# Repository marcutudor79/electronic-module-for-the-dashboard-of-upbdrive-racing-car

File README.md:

# ETTI-Bachelor's degree Applied Electronics

My Bachelor's degree that consists in research & design the following components:
- dashboard PCB with ESP32 SoC
- Test module PCB with Raspberry Pi Pico devboard
- Firmware for the ESP32 with ESP-IDF
- Firmware for the Raspberry Pi Pico with pico-sdk

# Thesis
The document can be referred [here.](Documentation/Thesis.pdf)

# Thesis summary
The thesis sumarry can be referred [here.](Documentation/Summary.pdf)

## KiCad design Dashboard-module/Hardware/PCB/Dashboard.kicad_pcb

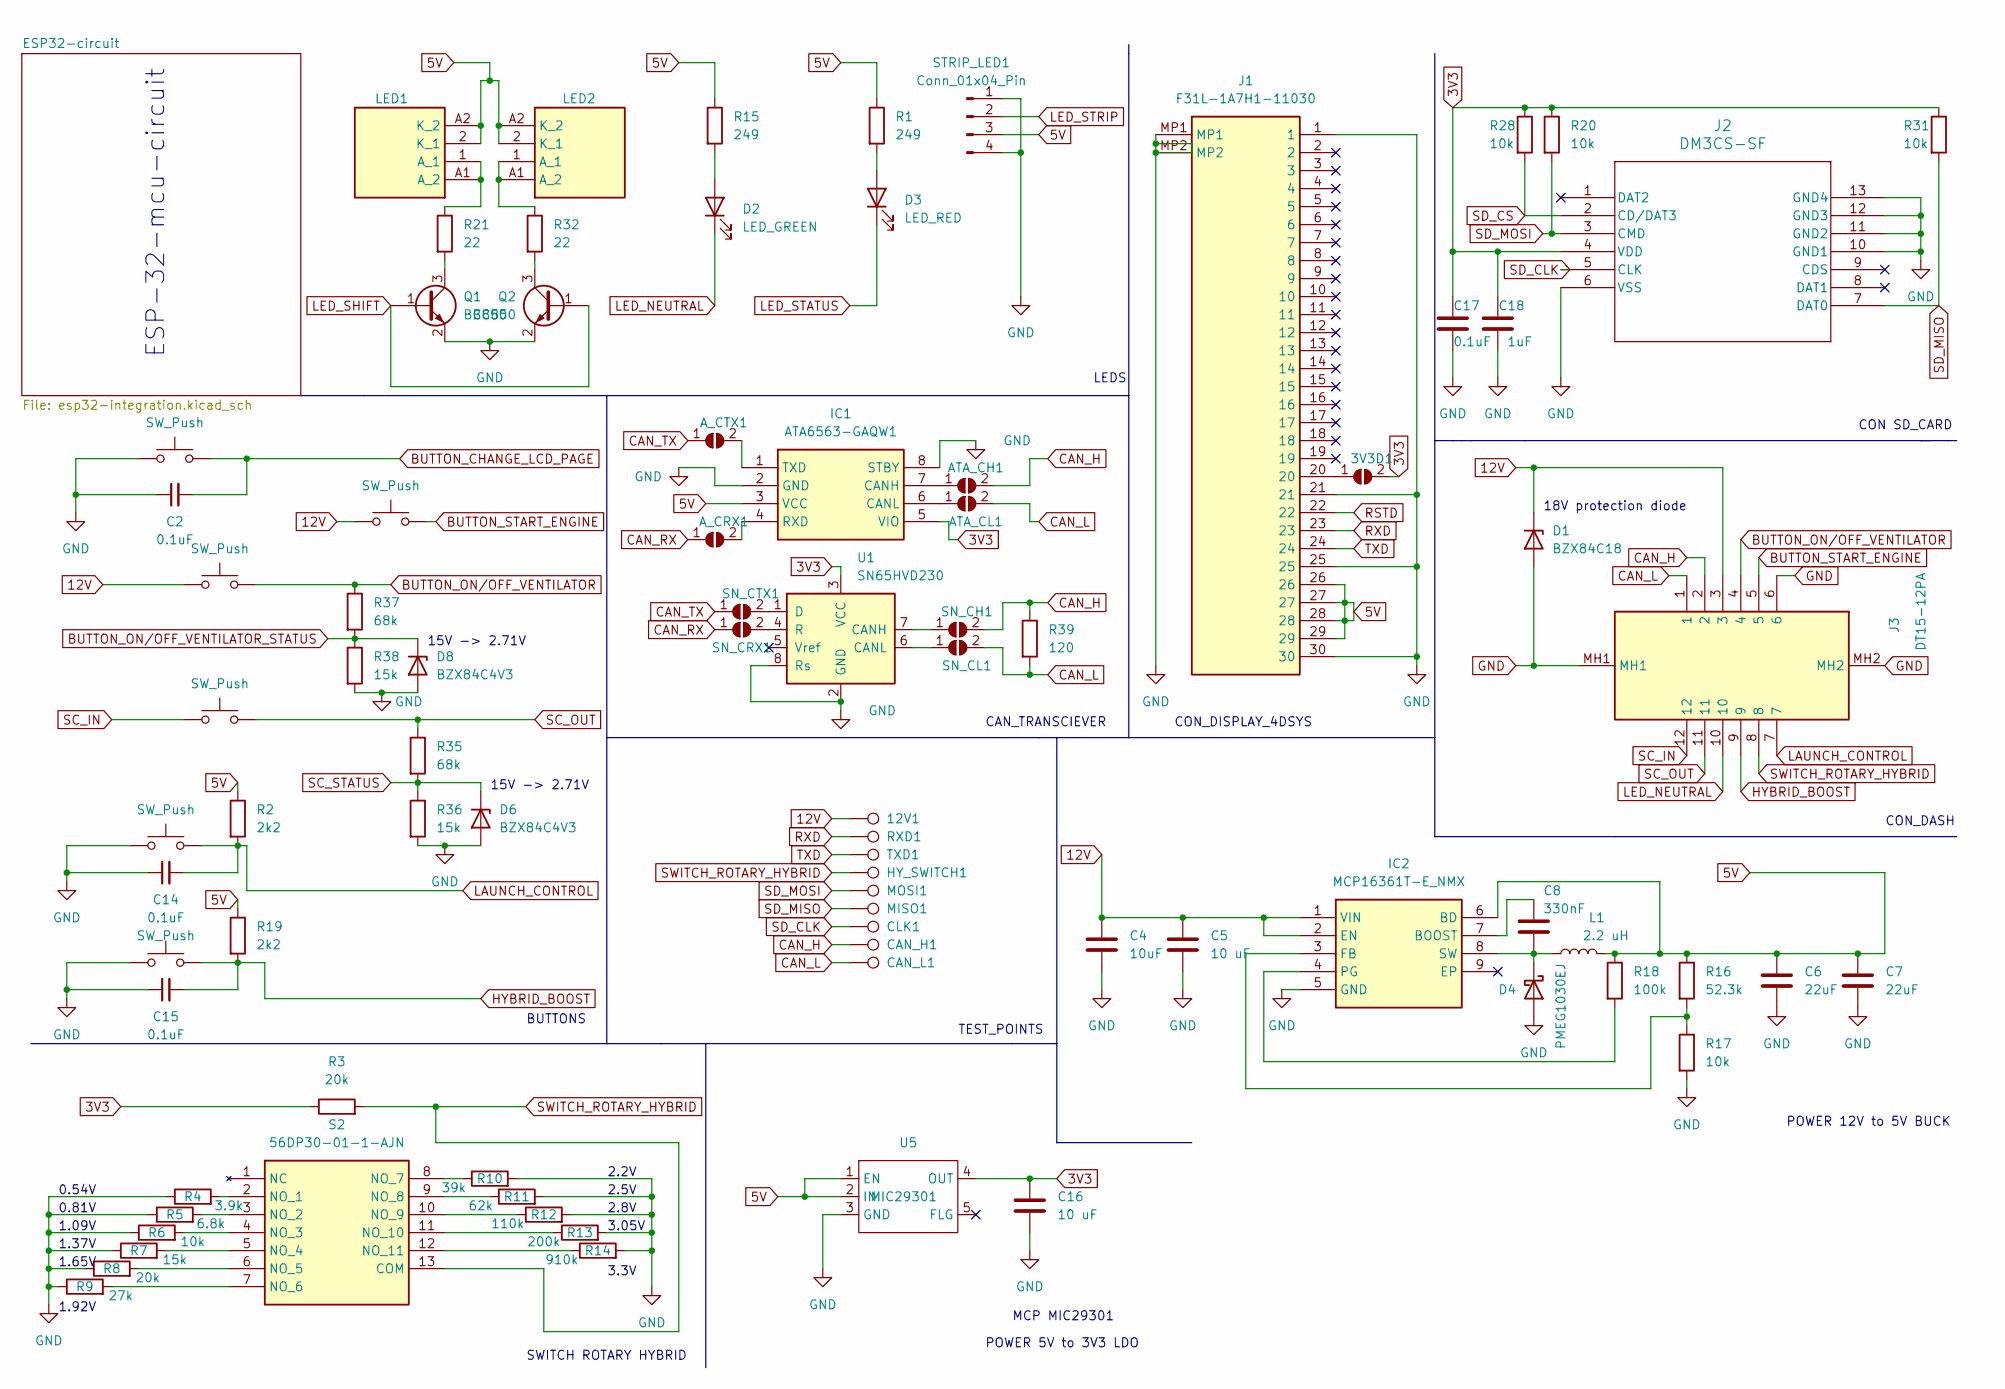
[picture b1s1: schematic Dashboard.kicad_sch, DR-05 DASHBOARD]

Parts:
3V3D1: SolderJumper_2_Open; SolderJumper-2_P1.3mm_Open_TrianglePad1.0x1.5mm
12V1: TestPoint; TestPoint_Pad_D2.0mm
ATA_CH1: SolderJumper_2_Open; SolderJumper-2_P1.3mm_Open_TrianglePad1.0x1.5mm
ATA_CL1: SolderJumper_2_Open; SolderJumper-2_P1.3mm_Open_TrianglePad1.0x1.5mm
A_CRX1: SolderJumper_2_Open; SolderJumper-2_P1.3mm_Open_TrianglePad1.0x1.5mm
A_CTX1: SolderJumper_2_Open; SolderJumper-2_P1.3mm_Open_TrianglePad1.0x1.5mm
BOOST1: SW_Push; PinHeader_1x02_P2.54mm_Vertical
C2, C14, C15, C17: 0.1uF; C_1210_3225Metric_Pad1.33x2.70mm_HandSolder
C4: 10uF; C_1210_3225Metric_Pad1.33x2.70mm_HandSolder
C5, C16: 10 uF; C_1210_3225Metric_Pad1.33x2.70mm_HandSolder
C6, C7: 22uF; C_1210_3225Metric_Pad1.33x2.70mm_HandSolder
C8: 330nF; C_1210_3225Metric_Pad1.33x2.70mm_HandSolder
C18: 1uF; C_1210_3225Metric_Pad1.33x2.70mm_HandSolder
CAN_H1: TestPoint; TestPoint_Pad_D2.0mm
CAN_L1: TestPoint; TestPoint_Pad_D2.0mm
CLK1: TestPoint; TestPoint_Pad_D2.0mm
D1: BZX84C18; SOT-23
D2: LED_GREEN; D_1210_3225Metric
D3: LED_RED; D_1210_3225Metric
D4: PMEG1030EJ; D_SOD-323_HandSoldering
D6, D8: BZX84C4V3; SOT-23
HY_SWITCH1: TestPoint; TestPoint_Pad_D2.0mm
IC1: ATA6563-GAQW1; SOIC127P600X175-8N; Mouser Part Number 579-ATA6563-GAQW1
IC2: MCP16361T-E_NMX; MCP16361TENMX; Mouser Part Number 579-MCP16361T-E/NMX
J1: F31L-1A7H1-11030; F31L1A7H111030; Mouser Part Number 649-F31L-1A7H1-11030
J2: DM3CS-SF; DM3CS_SF
J3: DT15-12PA; DT1512PA; Mouser Part Number 571-DT15-12PA
L1: 2.2 uH; L_Vishay_IHLP-5050
LAUNCH1: SW_Push; PinHeader_1x02_P2.54mm_Vertical
LED1, LED2: GR_PSLM31.23-FTGP-45-FG; GRPSLM3123FTGP45FG; Mouser Part Number 720-PSLM3123A4675
MISO1: TestPoint; TestPoint_Pad_D2.0mm
MOSI1: TestPoint; TestPoint_Pad_D2.0mm
PAGE1: SW_Push; PinHeader_1x02_P2.54mm_Vertical
Q1, Q2: BC850; SOT-23
R1, R15: 249; R_1210_3225Metric
R2, R19: 2k2; R_1210_3225Metric
R3, R8: 20k; R_1210_3225Metric_Pad1.30x2.65mm_HandSolder
R4: 3.9k; R_1210_3225Metric_Pad1.30x2.65mm_HandSolder
R5: 6.8k; R_1210_3225Metric_Pad1.30x2.65mm_HandSolder
R6, R17, R20, R28, R31: 10k; R_1210_3225Metric_Pad1.30x2.65mm_HandSolder
R7: 15k; R_1210_3225Metric_Pad1.30x2.65mm_HandSolder
R9: 27k; R_1210_3225Metric_Pad1.30x2.65mm_HandSolder
R10: 39k; R_1210_3225Metric_Pad1.30x2.65mm_HandSolder
R11: 62k; R_1210_3225Metric_Pad1.30x2.65mm_HandSolder
R12: 110k; R_1210_3225Metric_Pad1.30x2.65mm_HandSolder
R13: 200k; R_1210_3225Metric_Pad1.30x2.65mm_HandSolder
R14: 910k; R_1210_3225Metric_Pad1.30x2.65mm_HandSolder
R16: 52.3k; R_1210_3225Metric_Pad1.30x2.65mm_HandSolder
R18: 100k; R_1210_3225Metric_Pad1.30x2.65mm_HandSolder
R21, R32: 22; R_1210_3225Metric
R35, R37: 68k; R_1210_3225Metric
R36, R38: 15k; R_1210_3225Metric
R39: 120; R_1210_3225Metric_Pad1.30x2.65mm_HandSolder
RXD1: TestPoint; TestPoint_Pad_D2.0mm
S2: 56DP30-01-1-AJN; 56SP3001B12N; Mouser Part Number 706-56DP30-01-1-AJN
SC1: SW_Push; PinHeader_1x02_P2.54mm_Vertical
SN_CH1: SolderJumper_2_Open; SolderJumper-2_P1.3mm_Open_TrianglePad1.0x1.5mm
SN_CL1: SolderJumper_2_Open; SolderJumper-2_P1.3mm_Open_TrianglePad1.0x1.5mm
SN_CRX1: SolderJumper_2_Open; SolderJumper-2_P1.3mm_Open_TrianglePad1.0x1.5mm
SN_CTX1: SolderJumper_2_Open; SolderJumper-2_P1.3mm_Open_TrianglePad1.0x1.5mm
STRIP_LED1: Conn_01x04_Pin; PinSocket_1x04_P2.54mm_Vertical
S_ENG1: SW_Push; PinHeader_1x02_P2.54mm_Vertical
TXD1: TestPoint; TestPoint_Pad_D2.0mm
U1: SN65HVD230; SOIC-8_3.9x4.9mm_P1.27mm
U5: MIC29301; TO-220-5_Horizontal_TabDown
VENT1: SW_Push; PinHeader_1x02_P2.54mm_Vertical

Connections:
3V3: 3V3D1.2 (B), C16.1, C17.1, C18.1, IC1.5 (VIO), J2.4 (VDD), R3.1, R20.1, R28.1, R31.1, U1.3 (VCC), U5.4 (OUT); also elsewhere on the board
5V: C6.1, C7.1, IC1.3 (VCC), IC2.6 (BD), J1.26, J1.27, J1.28, J1.29, L1.2, LED1.2 (K_1), LED1.A2 (K_2), LED2.2 (K_1), LED2.A2 (K_2), R1.1, R2.1, R15.1, R16.1, R18.1, R19.1, STRIP_LED1.3, U5.1 (EN), U5.2 (IN); also elsewhere on the board
12V: 12V1.1, C4.1, C5.1, D1.3 (K), IC2.1 (VIN), IC2.2 (EN), J3.3, S_ENG1.2, VENT1.2
BUTTON_CHANGE_LCD_PAGE: C2.2, PAGE1.2; also elsewhere on the board
BUTTON_ON/OFF_VENTILATOR: J3.4, R37.1, VENT1.1
BUTTON_ON/OFF_VENTILATOR_STATUS: D8.3 (K), R37.2, R38.1; also elsewhere on the board
BUTTON_START_ENGINE: J3.5, S_ENG1.1
CAN_H: ATA_CH1.2 (B), CAN_H1.1, J3.2, R39.1, SN_CH1.2 (B)
CAN_L: ATA_CL1.2 (B), CAN_L1.1, J3.1, R39.2, SN_CL1.2 (B)
CAN_RX: A_CRX1.1 (A), SN_CRX1.1 (A); also elsewhere on the board
CAN_TX: A_CTX1.1 (A), SN_CTX1.1 (A); also elsewhere on the board
GND: BOOST1.2, C2.1, C4.2, C5.2, C6.2, C7.2, C14.1, C15.1, C16.2, C17.2, C18.2, D1.1 (A), D4.2 (A), D6.1 (A), D8.1 (A), IC1.2 (GND), IC1.8 (STBY), IC2.5 (GND), J1.1, J1.21, J1.25, J1.30, J1.MP1, J1.MP2, J2.6 (VSS), J2.10 (GND1), J2.11 (GND2), J2.12 (GND3), J2.13 (GND4), J3.6, J3.MH1, J3.MH2, LAUNCH1.2, PAGE1.1, Q1.2 (E), Q2.2 (E), R4.1, R5.1, R6.1, R7.1, R8.1, R9.1, R10.2, R11.2, R12.2, R13.2, R14.2, R17.2, R36.2, R38.2, STRIP_LED1.1, STRIP_LED1.4, U1.2 (GND), U1.8 (Rs), U5.3 (GND); also elsewhere on the board
HYBRID_BOOST: BOOST1.1, C15.2, J3.9, R19.2
LAUNCH_CONTROL: C14.2, J3.7, LAUNCH1.1, R2.2
LED_NEUTRAL: D2.1 (K), J3.10; also elsewhere on the board
LED_SHIFT: Q1.1 (B), Q2.1 (B); also elsewhere on the board
LED_STATUS: D3.1 (K); also elsewhere on the board
LED_STRIP: STRIP_LED1.2; also elsewhere on the board
unnamed: 3V3D1.1 (A), J1.20
unnamed: ATA_CH1.1 (A), IC1.7 (CANH)
unnamed: ATA_CL1.1 (A), IC1.6 (CANL)
unnamed: A_CRX1.2 (B), IC1.4 (RXD)
unnamed: A_CTX1.2 (B), IC1.1 (TXD)
unnamed: D2.2 (A), R15.2
unnamed: D3.2 (A), R1.2
unnamed: C8.2, D4.1 (K), IC2.8 (SW), L1.1
unnamed: C8.1, IC2.7 (BOOST)
unnamed: IC2.3 (FB), R16.2, R17.1
unnamed: IC2.4 (PG), R18.2
unnamed: LED1.1 (A_1), LED1.A1 (A_2), R21.1
unnamed: LED2.1 (A_1), LED2.A1 (A_2), R32.1
unnamed: Q1.3 (C), R21.2
unnamed: Q2.3 (C), R32.2
unnamed: R4.2, S2.2 (NO_1)
unnamed: R5.2, S2.3 (NO_2)
unnamed: R6.2, S2.4 (NO_3)
unnamed: R7.2, S2.5 (NO_4)
unnamed: R8.2, S2.6 (NO_5)
unnamed: R9.2, S2.7 (NO_6)
unnamed: R10.1, S2.8 (NO_7)
unnamed: R11.1, S2.9 (NO_8)
unnamed: R12.1, S2.10 (NO_9)
unnamed: R13.1, S2.11 (NO_10)
unnamed: R14.1, S2.12 (NO_11)
unnamed: SN_CH1.1 (A), U1.7 (CANH)
unnamed: SN_CL1.1 (A), U1.6 (CANL)
unnamed: SN_CRX1.2 (B), U1.4 (R)
unnamed: SN_CTX1.2 (B), U1.1 (D)
RSTD: J1.22; also elsewhere on the board
RXD: J1.23, RXD1.1; also elsewhere on the board
SC_IN: J3.12, SC1.2
SC_OUT: J3.11, R35.1, SC1.1
SC_STATUS: D6.3 (K), R35.2, R36.1; also elsewhere on the board
SD_CLK: CLK1.1, J2.5 (CLK); also elsewhere on the board
SD_CS: J2.2 (CD/DAT3), R28.2; also elsewhere on the board
SD_MISO: J2.7 (DAT0), MISO1.1, R31.2; also elsewhere on the board
SD_MOSI: J2.3 (CMD), MOSI1.1, R20.2; also elsewhere on the board
SWITCH_ROTARY_HYBRID: HY_SWITCH1.1, J3.8, R3.2, S2.13 (COM); also elsewhere on the board
TXD: J1.24, TXD1.1; also elsewhere on the board

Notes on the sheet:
2.2V
1.37V
BUTTONS
1.65V
TEST_POINTS
POWER 5V to 3V3 LDO
0.54V
CON SD_CARD
LEDS
3.3V
CON_DASH
CAN_TRANSCIEVER
15V -> 2.71V
0.81V
SWITCH ROTARY HYBRID
2.8V
CON_DISPLAY_4DSYS
1.92V
2.5V
1.09V
3.05V
ESP-32-mcu-circuit
POWER 12V to 5V BUCK
18V protection diode
MCP MIC29301

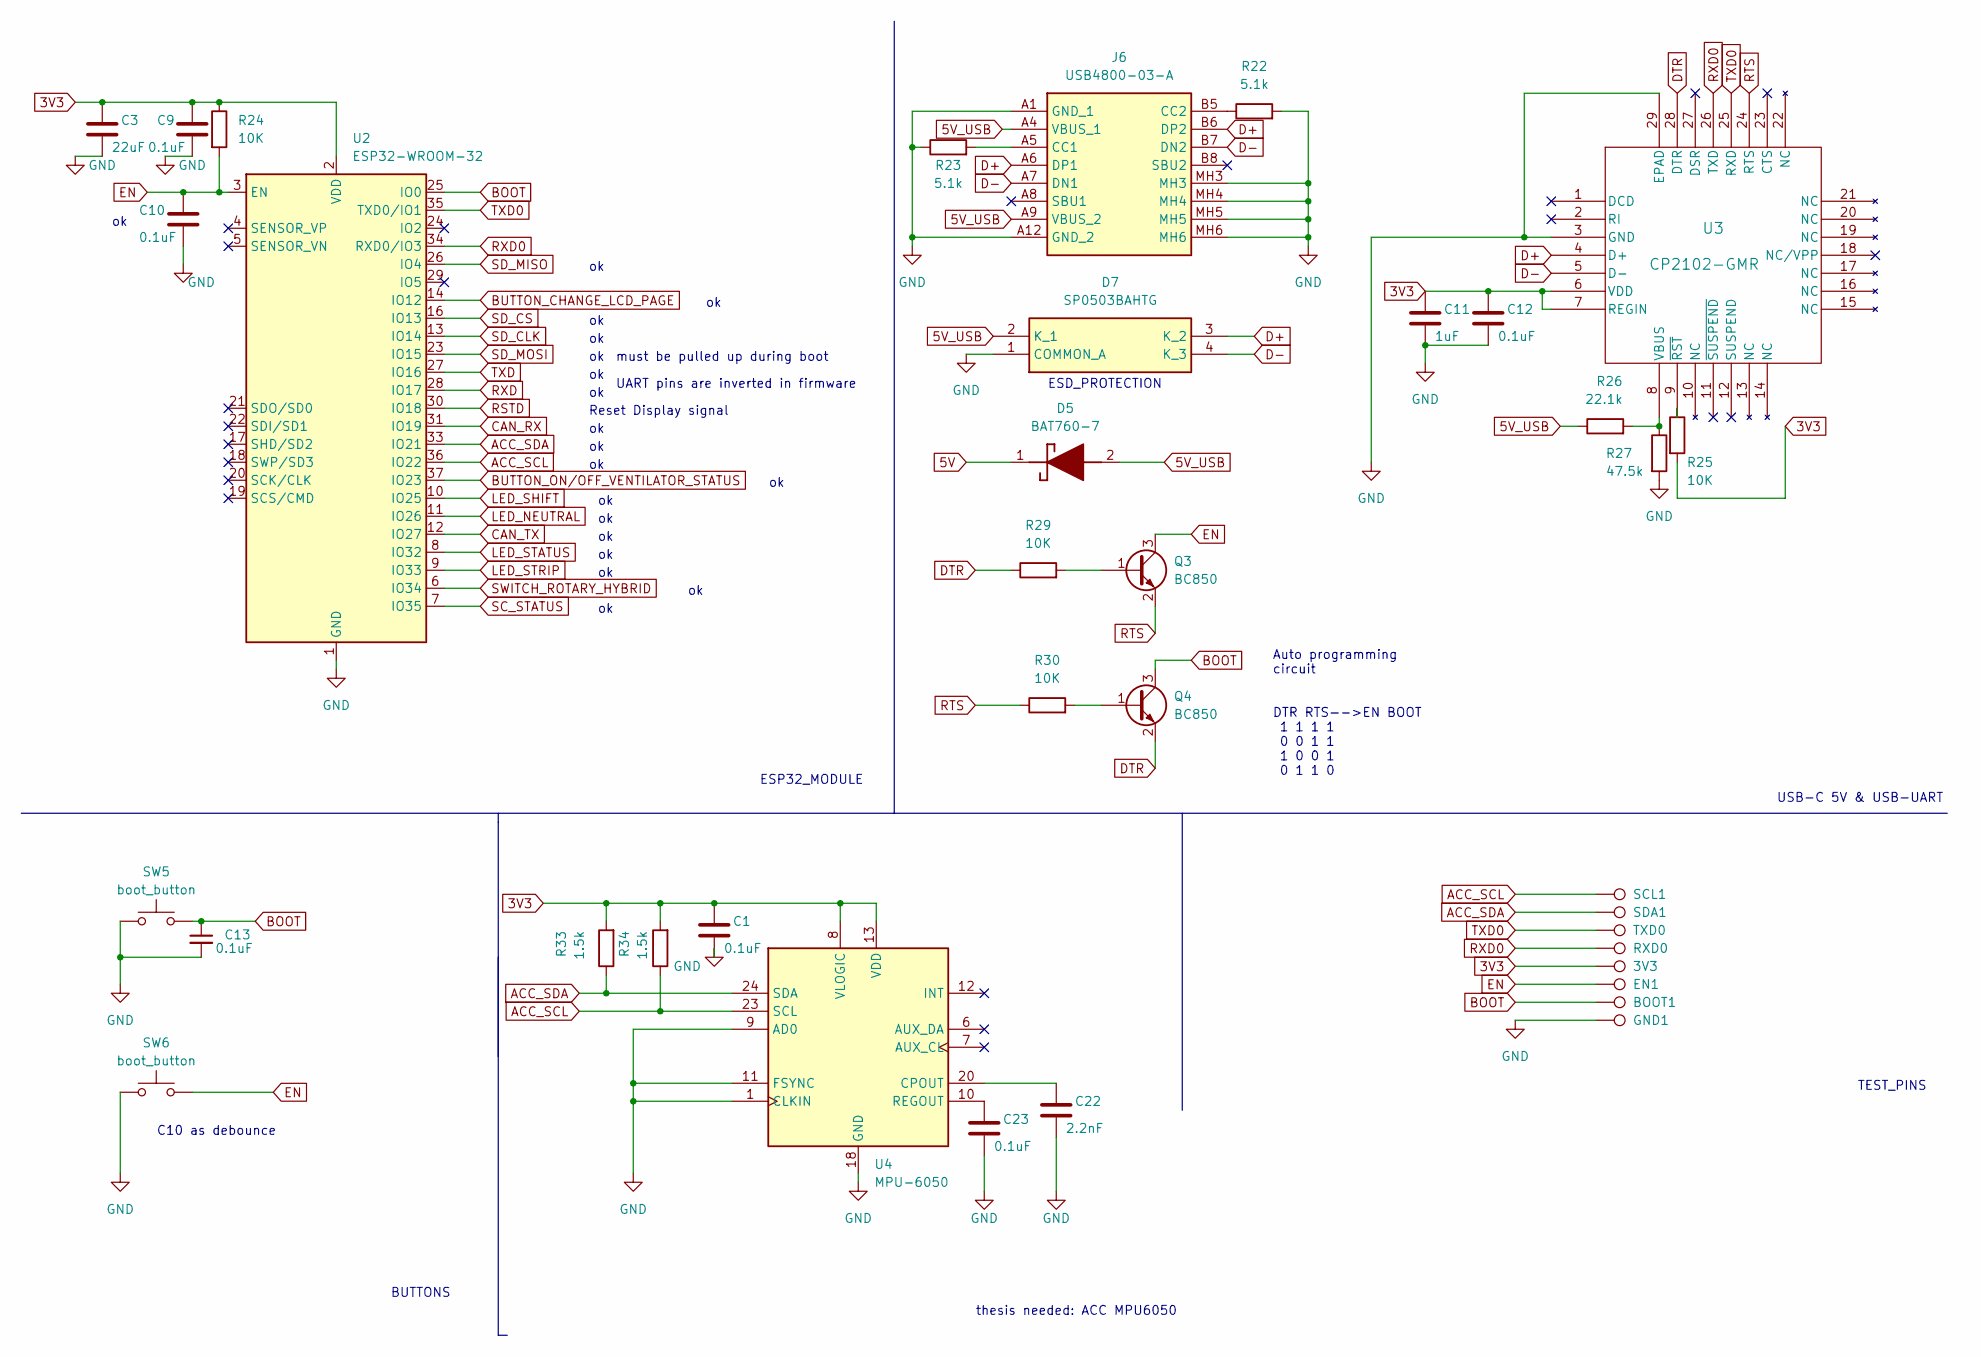
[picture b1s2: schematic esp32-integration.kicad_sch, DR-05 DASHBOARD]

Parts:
3V3: TestPoint; TestPoint_Pad_D2.0mm
BOOT1: TestPoint; TestPoint_Pad_D2.0mm
C1, C9, C10, C12, C23: 0.1uF; C_1210_3225Metric_Pad1.33x2.70mm_HandSolder
C3: 22uF; C_1210_3225Metric_Pad1.33x2.70mm_HandSolder
C11: 1uF; C_1210_3225Metric_Pad1.33x2.70mm_HandSolder
C13: 0.1uF; C_1210_3225Metric_Pad1.33x2.70mm_HandSolder; Manufacturer_Part_Number C1210C104K5RACAUTO
C22: 2.2nF; C_1210_3225Metric_Pad1.33x2.70mm_HandSolder
D5: BAT760-7; Mouser Part Number 621-BAT760-7
D7: SP0503BAHTG; Mouser Part Number 576-SP0503BAHTG
EN1: TestPoint; TestPoint_Pad_D2.0mm
GND1: TestPoint; TestPoint_Pad_D2.0mm
J6: USB4800-03-A; USB480003A; Mouser Part Number 640-USB4800-03-A
Q3, Q4: BC850; SOT-23
R22, R23: 5.1k; R_1210_3225Metric_Pad1.30x2.65mm_HandSolder
R24, R25, R29, R30: 10K; R_1210_3225Metric_Pad1.30x2.65mm_HandSolder
R26: 22.1k; R_1210_3225Metric_Pad1.30x2.65mm_HandSolder
R27: 47.5k; R_1210_3225Metric_Pad1.30x2.65mm_HandSolder
R33, R34: 1.5k; R_1210_3225Metric_Pad1.30x2.65mm_HandSolder
RXD0: TestPoint; TestPoint_Pad_D2.0mm
SCL1: TestPoint; TestPoint_Pad_D2.0mm
SDA1: TestPoint; TestPoint_Pad_D2.0mm
SW5, SW6: boot_button; SW_Tactile_SPST_NO_Straight_CK_PTS636Sx25SMTRLFS; Manufacturer_Part_Number PTS636 SK25 SMTR LFS
TXD0: TestPoint; TestPoint_Pad_D2.0mm
U2: ESP32-WROOM-32
U3: CP2102-GMR; QFN28_5X5_SIL
U4: MPU-6050; InvenSense_QFN-24_4x4mm_P0.5mm

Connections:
3V3: 3V3.1, C1.1, C3.1, C9.1, C11.1, C12.1, R24.1, R25.2, R33.2, R34.2, U2.2 (VDD), U3.6 (VDD), U3.7 (REGIN), U4.8 (VLOGIC), U4.13 (VDD); also elsewhere on the board
5V: D5.1 (K); also elsewhere on the board
5V_USB: D5.2 (A), D7.2 (K_1), J6.A4 (VBUS_1), J6.A9 (VBUS_2), R26.1
ACC_SCL: R34.1, SCL1.1, U2.36 (IO22), U4.23 (SCL)
ACC_SDA: R33.1, SDA1.1, U2.33 (IO21), U4.24 (SDA)
BOOT: BOOT1.1, C13.1, Q4.3 (C), SW5.2, U2.25 (IO0)
BUTTON_CHANGE_LCD_PAGE: U2.14 (IO12); also elsewhere on the board
BUTTON_ON/OFF_VENTILATOR_STATUS: U2.37 (IO23); also elsewhere on the board
CAN_RX: U2.31 (IO19); also elsewhere on the board
CAN_TX: U2.12 (IO27); also elsewhere on the board
D+: D7.3 (K_2), J6.A6 (DP1), J6.B6 (DP2), U3.4 (D+)
D-: D7.4 (K_3), J6.A7 (DN1), J6.B7 (DN2), U3.5 (D-)
DTR: Q4.2 (E), R29.1, U3.28 (DTR)
EN: C10.1, EN1.1, Q3.3 (C), R24.2, SW6.2, U2.3 (EN)
GND: C1.2, C3.2, C9.2, C10.2, C11.2, C12.2, C13.2, C22.2, C23.2, D7.1 (COMMON_A), GND1.1, J6.A1 (GND_1), J6.A12 (GND_2), J6.MH3, J6.MH4, J6.MH5, J6.MH6, R22.2, R23.1, R27.2, SW5.1, SW6.1, U2.1 (GND), U2.15 (GND), U2.38 (GND), U2.39 (GND), U3.3 (GND), U3.29 (EPAD), U4.1 (CLKIN), U4.9 (AD0), U4.11 (FSYNC), U4.18 (GND); also elsewhere on the board
LED_NEUTRAL: U2.11 (IO26); also elsewhere on the board
LED_SHIFT: U2.10 (IO25); also elsewhere on the board
LED_STATUS: U2.8 (IO32); also elsewhere on the board
LED_STRIP: U2.9 (IO33); also elsewhere on the board
unnamed: J6.A5 (CC1), R23.2
unnamed: J6.B5 (CC2), R22.1
unnamed: Q3.1 (B), R29.2
unnamed: Q4.1 (B), R30.2
unnamed: R26.2, R27.1, U3.8 (VBUS)
unnamed: R25.1, U3.9 (~RST)
unnamed: C22.1, U4.20 (CPOUT)
unnamed: C23.1, U4.10 (REGOUT)
RSTD: U2.30 (IO18); also elsewhere on the board
RTS: Q3.2 (E), R30.1, U3.24 (RTS)
RXD: U2.28 (IO17); also elsewhere on the board
RXD0: RXD0.1, U2.34 (RXD0/IO3), U3.26 (TXD)
SC_STATUS: U2.7 (IO35); also elsewhere on the board
SD_CLK: U2.13 (IO14); also elsewhere on the board
SD_CS: U2.16 (IO13); also elsewhere on the board
SD_MISO: U2.26 (IO4); also elsewhere on the board
SD_MOSI: U2.23 (IO15); also elsewhere on the board
SWITCH_ROTARY_HYBRID: U2.6 (IO34); also elsewhere on the board
TXD: U2.27 (IO16); also elsewhere on the board
TXD0: TXD0.1, U2.35 (TXD0/IO1), U3.25 (RXD)

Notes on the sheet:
Auto programming circuit DTR RTS-->EN BOOT 1 1 1 1 0 0 1 1 1 0 0 1 0 1 1 0
C10 as debounce
ESP32_MODULE
ESD_PROTECTION
BUTTONS
must be pulled up during boot
USB-C 5V & USB-UART
thesis needed: ACC MPU6050
Reset Display signal
TEST_PINS
UART pins are inverted in firmware

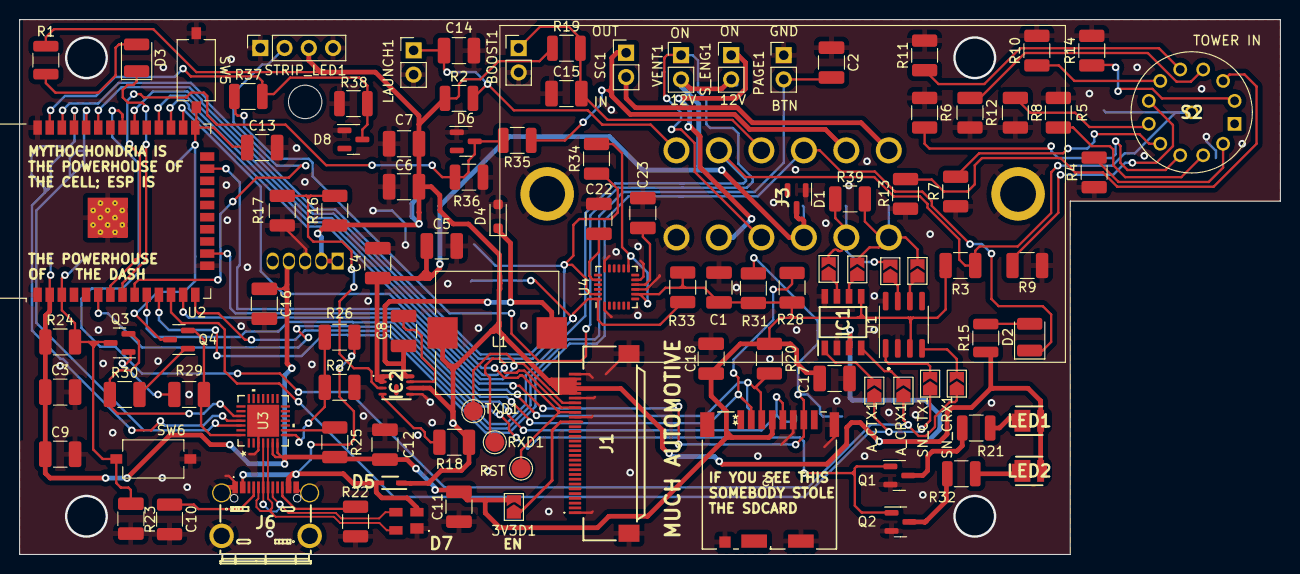
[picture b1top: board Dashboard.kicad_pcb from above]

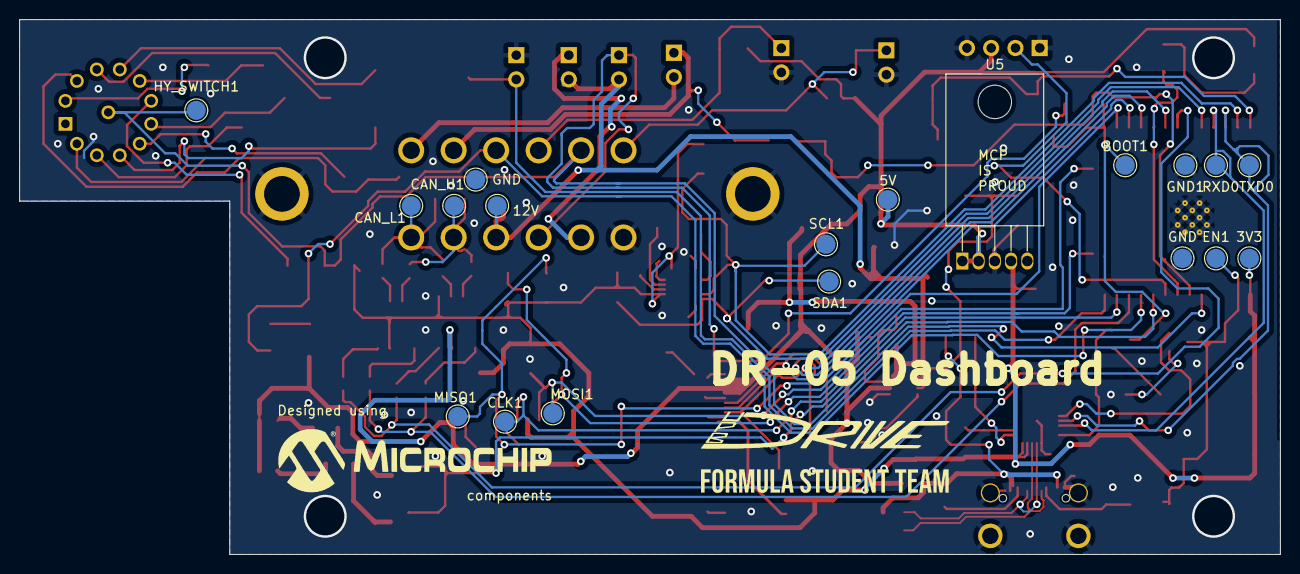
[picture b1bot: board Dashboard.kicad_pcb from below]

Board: 2 copper layers, 132.0 x 56.0 mm, 125 parts (19 on the bottom side), 78 nets.

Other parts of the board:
5V: TestPoint; TestPoint_Pad_D2.0mm
GND: TestPoint; TestPoint_Pad_D2.0mm
GND#2: TestPoint; TestPoint_Pad_D2.0mm
RST: TestPoint; TestPoint_Pad_D2.0mm

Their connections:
5V: 5V.1; also elsewhere on the board
GND: GND.1, GND#2.1; also elsewhere on the board
RSTD: RST.1; also elsewhere on the board

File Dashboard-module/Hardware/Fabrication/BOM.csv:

"Reference","Value","Mouser Price/Stock","Qty"
"3V3","TestPoint","","1"
"3V3D1","SolderJumper_2_Open","","1"
"12V1","TestPoint","","1"
"ATA_CH1","SolderJumper_2_Open","","1"
"ATA_CL1","SolderJumper_2_Open","","1"
"A_CRX1","SolderJumper_2_Open","","1"
"A_CTX1","SolderJumper_2_Open","","1"
"BOOST1","SW_Push","","1"
"BOOT1","TestPoint","","1"
"C1, C2, C9, C10, C12-C15, C17, C23","0.1uF","https://ro.mouser.com/ProductDetail/KEMET/C1210C104K5RACAUTO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","10"
"C3, C6, C7","22uF","https://www.mouser.co.uk/ProductDetail/Samsung-Electro-Mecha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","3"
"C4","10uF","https://www.mouser.co.uk/ProductDetail/Samsung-Electro-Mecha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","1"
"C5, C16","10 uF","https://www.mouser.co.uk/ProductDetail/Samsung-Electro-Mecha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","2"
"C8","330nF","https://ro.mouser.com/ProductDetail/KEMET/C1210C334J3RACTU?q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","1"
"C11, C18","1uF","https://ro.mouser.com/ProductDetail/KEMET/C1210C105K5RACAUTO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","2"
"C22","2.2nF","https://ro.mouser.com/ProductDetail/KEMET/C1210C222KGRACAUTO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","1"
"CAN_H1","TestPoint","","1"
"CAN_L1","TestPoint","","1"
"CLK1","TestPoint","","1"
"D1","BZX84C18","https://eu.mouser.com/ProductDetail/Diotec-Semiconductor/BZX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","1"
"D2","LED_GREEN","https://www.mouser.co.uk/ProductDetail/Broadcom-Avago/ASMT-B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","1"
"D3","LED_RED","https://www.mouser.co.uk/ProductDetail/Broadcom-Avago/ASMT-B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","1"
"D4","PMEG1030EJ","https:/ro.mouser.com/ProductDetail/Nexperia/PMEG1030EJ115?qs=LOCUfHb8d9vmk7P%2FuYbs5A%3D%3D","1"
"D5","BAT760-7","https://www.mouser.co.uk/ProductDetail/Diodes-Incorporated/B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","1"
"D6, D8","BZX84C4V3","https://eu.mouser.com/ProductDetail/Diotec-Semiconductor/BZX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","2"
"D7","SP0503BAHTG","https://www.mouser.co.uk/ProductDetail/Littelfuse/SP0503BAHT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","1"
"EN1","TestPoint","","1"
"GND1","TestPoint","","1"
"HY_SWITCH1","TestPoint","","1"
"IC1","ATA6563-GAQW1","https://www.mouser.co.uk/ProductDetail/Microchip-Technology/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","1"
"IC2","MCP16361T-E_NMX","https://www.mouser.co.uk/ProductDetail/Microchip-Technology/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","1"
"J1","F31L-1A7H1-11030","https://www.mouser.co.uk/ProductDetail/Amphenol-Aorora/F31L-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","1"
"J2","DM3CS-SF","https://eu.mouser.com/ProductDetail/Hirose-Connector/DM3CS-S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","1"
"J3","DT15-12PA","https://www.mouser.co.uk/ProductDetail/TE-Connectivity-DEUTS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","1"
"J6","USB4800-03-A","https://www.mouser.co.uk/ProductDetail/GCT/USB4800-03-A?qs=v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","1"
"L1","2.2 uH","https://www.mouser.co.uk/ProductDetail/Vishay-Dale/IHLP5050C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","1"
"LAUNCH1","SW_Push","","1"
"LED1, LED2","GR_PSLM31.23-FTGP-45-FG","https://www.mouser.co.uk/ProductDetail/OSRAM-Opto-Semiconduc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","2"
"MISO1","TestPoint","","1"
"MOSI1","TestPoint","","1"
"PAGE1","SW_Push","","1"
"Q1-Q4","BC850","https://www.mouser.co.uk/ProductDetail/Infineon-Technologies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","4"
"R1, R15","249","https://www.mouser.co.uk/ProductDetail/YAGEO/AC1210FR-07249R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","2"
"R2, R19","2k2","https://www.mouser.co.uk/ProductDetail/YAGEO/RC1210JR-072K2L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","2"
"R3, R8","20k","https://www.mouser.co.uk/c/passive-components/resistors/film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","2"
"R4","3.9k","https://www.mouser.co.uk/ProductDetail/YAGEO/AC1210FR-073K9L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","1"
"R5","6.8k","https://www.mouser.co.uk/ProductDetail/YAGEO/AC1210JR-076K8L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","1"
"R6, R17, R20, R28, R31","10k","-- mixed values --","5"
"R7, R36, R38","15k","-- mixed values --","3"
"R9","27k","https://www.mouser.co.uk/ProductDetail/YAGEO/RC1210JR-0727KL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","1"
"R10","39k","https://www.mouser.co.uk/ProductDetail/YAGEO/AC1210FR-0739KL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","1"
"R11","62k","https://www.mouser.co.uk/ProductDetail/YAGEO/RC1210FR-0762KL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","1"
"R12","110k","https://www.mouser.co.uk/ProductDetail/YAGEO/RC1210FR-07110K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","1"
"R13","200k","https://www.mouser.co.uk/ProductDetail/YAGEO/RC1210JR-07200K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","1"
"R14","910k","https://www.mouser.co.uk/c/passive-components/resistors/film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","1"
"R16","52.3k","https://ro.mouser.com/ProductDetail/Panasonic/ERJ-14NF5232U?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","1"
"R18","100k","https://ro.mouser.com/c/?q=RC1210FR-07100KL","1"
"R21, R32","22","https://www.mouser.co.uk/ProductDetail/YAGEO/AC1210JR-0722RL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","2"
"R22, R23","5.1k","https://www.mouser.co.uk/ProductDetail/YAGEO/RC1210FR-075K1L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","2"
"R24, R25, R29, R30","10K","https://ro.mouser.com/ProductDetail/SEI-Stackpole/RMCF1210FT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","4"
"R26","22.1k","https://ro.mouser.com/ProductDetail/Vishay-Dale/CRCW121022K1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","1"
"R27","47.5k","https://ro.mouser.com/ProductDetail/Vishay-Dale/CRCW121047K5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","1"
"R33, R34","1.5k","https://www.mouser.co.uk/ProductDetail/YAGEO/RC1210JR-071K5L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","2"
"R35, R37","68k","-- mixed values --","2"
"R39","120","https://www.mouser.co.uk/ProductDetail/YAGEO/RC1210JR-13120R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","1"
"RXD0, RXD1","TestPoint","","2"
"S2","56DP30-01-1-AJN","https://www.mouser.co.uk/ProductDetail/Grayhill/56DP30-01-1-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","1"
"SC1","SW_Push","","1"
"SCL1","TestPoint","","1"
"SDA1","TestPoint","","1"
"SN_CH1","SolderJumper_2_Open","","1"
"SN_CL1","SolderJumper_2_Open","","1"
"SN_CRX1","SolderJumper_2_Open","","1"
"SN_CTX1","SolderJumper_2_Open","","1"
"STRIP_LED1","Conn_01x04_Pin","https://www.mouser.co.uk/ProductDetail/Harwin/M20-9992046?qs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","1"
"SW5, SW6","boot_button","https://ro.mouser.com/ProductDetail/CK/PTS636-SK25-SMTR-LFS?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","2"
"S_ENG1","SW_Push","","1"
"TXD0, TXD1","TestPoint","","2"
"U1","SN65HVD230","https://eu.mouser.com/ProductDetail/Texas-Instruments/SN65HV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","1"
"U2","ESP32-WROOM-32","https://ro.mouser.com/ProductDetail/Espressif-Systems/ESP32-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","1"
"U3","CP2102-GMR","https://ro.mouser.com/ProductDetail/Silicon-Labs/CP2102-GMR?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","1"
"U4","MPU-6050","https://www.mouser.co.uk/ProductDetail/TDK-InvenSense/MPU-60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","1"
"U5","MIC29301","","1"
"VENT1","SW_Push","","1"

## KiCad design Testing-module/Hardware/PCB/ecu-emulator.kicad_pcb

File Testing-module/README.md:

# ECU Emulator

## Description
In order to debug the CAN bus as well as the dashboard module, this ECU Emulator
injects CAN packets into the CAN bus. It is a replacement for the ECU itself, because
we cannot use it just for electronics debugging, it has to be mounted in the FS car.

## How does it work
This ECU Emulator uses a potentiometer to emulate the accelerator pedal of the FS car
as well as a button to emulate the gear shift. The potentiometer is read via the built-in
ADC module of the Raspberry Pi Pico board, and the button is read using GPIO functions.

### How is the data generated
- rpm is generated using a constant 800 + the potentiometer value + a random number
between 0 - 49 in order to emulate the actual rpm of the FS car. The expected range is
between 800 - 13000.
- current gear is initially 0 (netural) and incremented when the button is pressed, until 4,
then it is set back to 0.
- all the other data is assigned the saw tooth signal between 0 - 250.

The CAN packets are formatted with respect to the CAN Packet allocation excel and then sent via the CAN bus.

## Project structure
```
- Docs     /* folder the documentation files */
- Firmware /
            - components/ - adc                 /* part of the code that enables the onboard
                                                    adc and configures a gpio to read a button */
                          - can                 /* part of the code that enables can communication
                                                    via the can bus transciever
                                                    also formats the packets according to the CAN
                                                    packet allocation */
                          - common              /* contains a header file in which the pins used
                                                    in the project are defined */
                          - heartbeat           /* part of the code that enables the built-in LED
                                                    to blink, for debug purposes */
                          - signal-generation   /* part of the code that generates the rpm data,
                                                   CurrentGear data and a sawtooth signal that
                                                   will replace the other data in the CAN packets */
            - main                /* contains the main source and header file with
                                    which describes the main loop of the program */
            - modules             /* contains can2040 git submodule that enables
                                     the PICO to communicate via CAN using bit banging
                                     on GPIOs */

- README.md /* project README file */
```

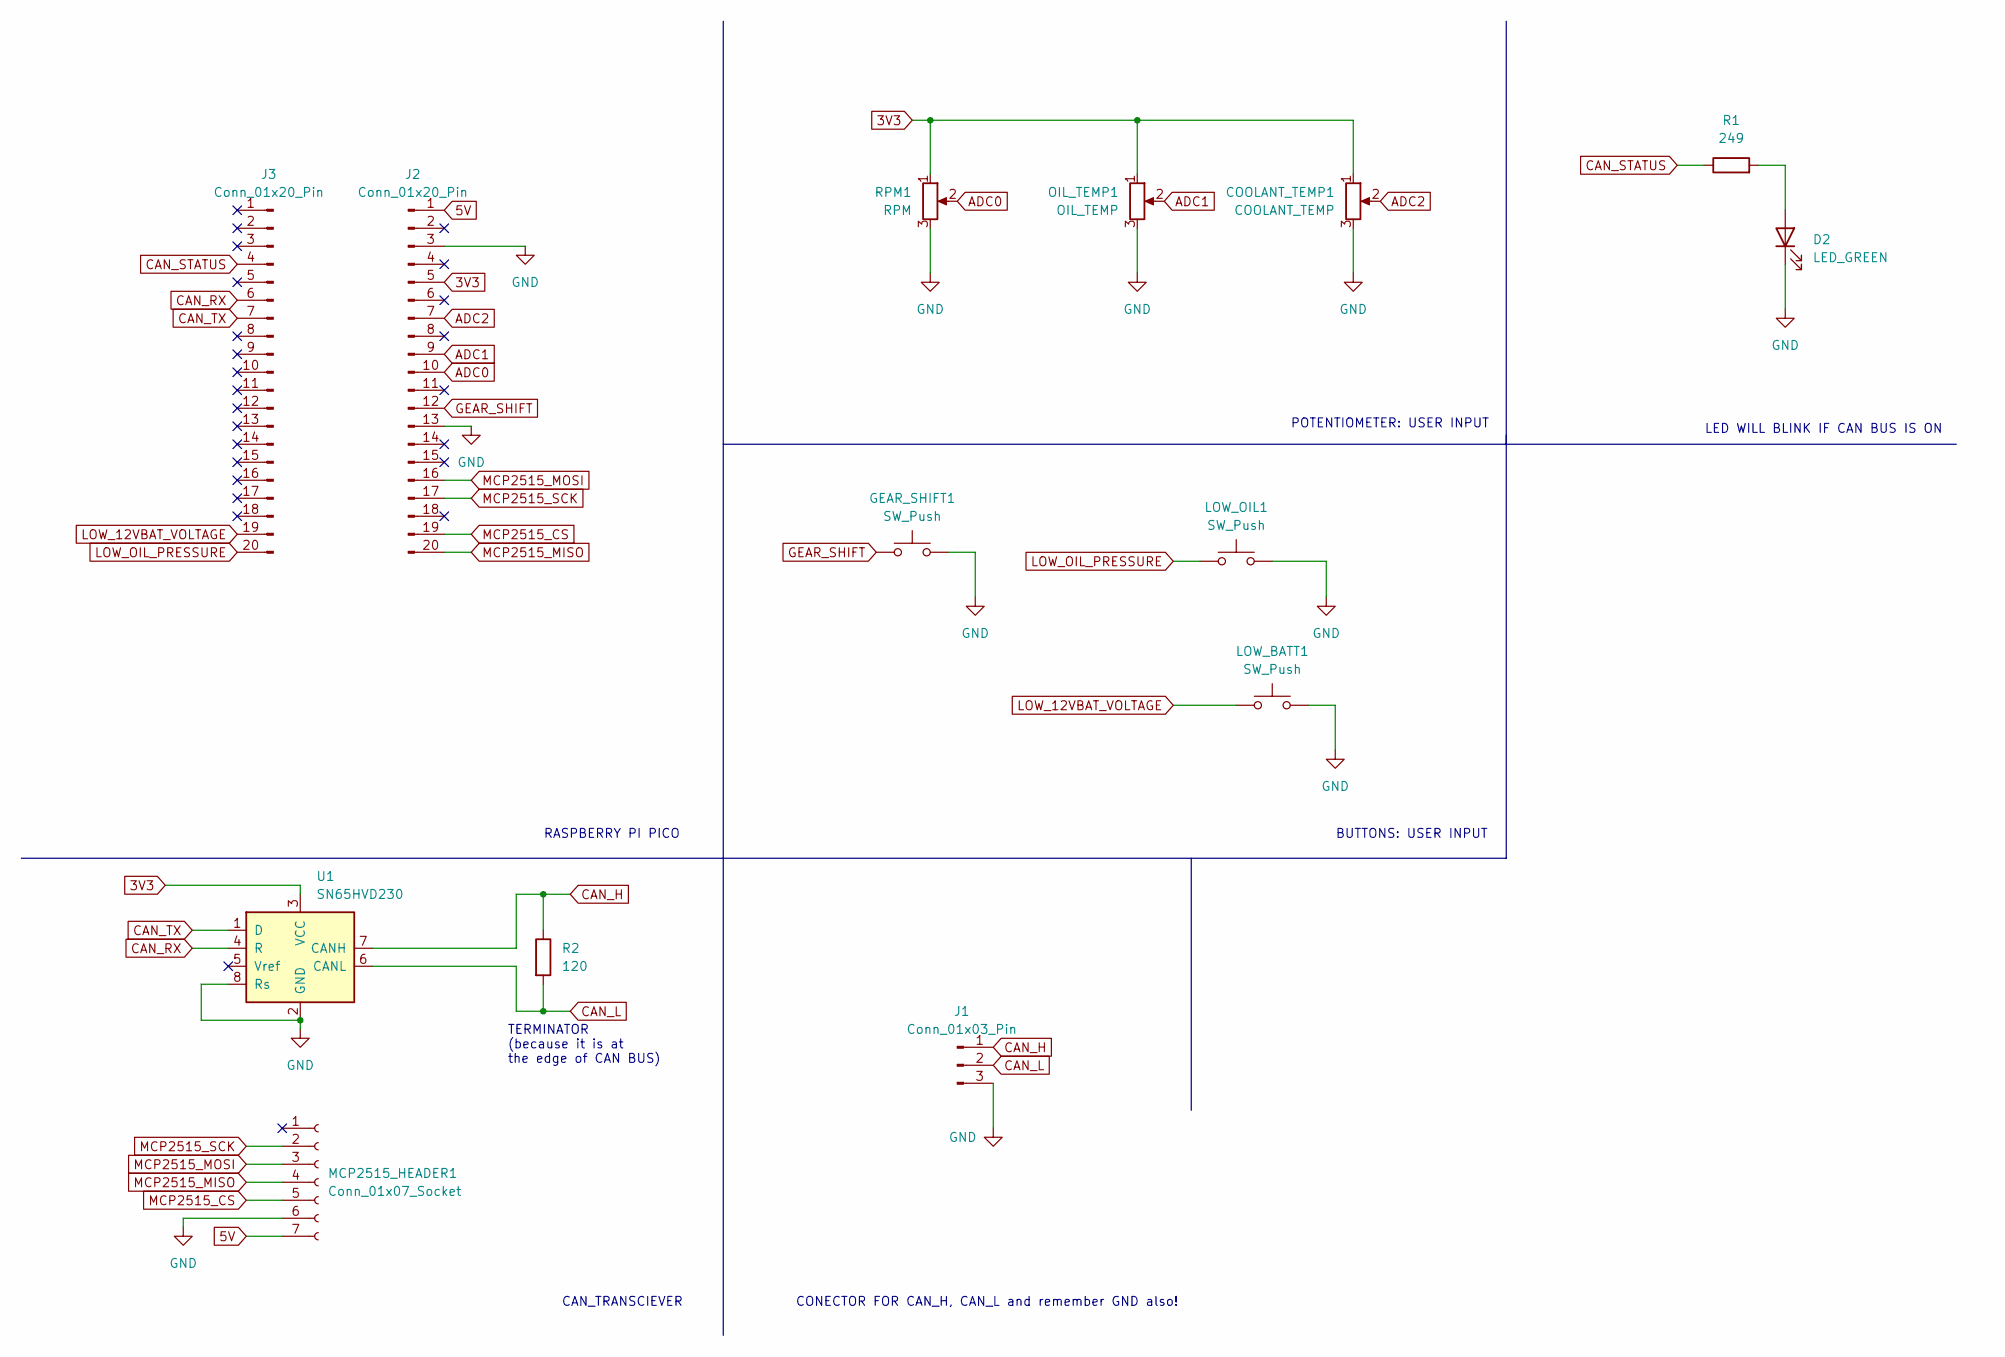
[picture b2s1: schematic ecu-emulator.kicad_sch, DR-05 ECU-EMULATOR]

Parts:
COOLANT_TEMP1: COOLANT_TEMP; Potentiometer_Alps_RK163_Single_Horizontal
D2: LED_GREEN; D_1210_3225Metric
GEAR_SHIFT1: SW_Push; SW_PUSH_6mm
J1: Conn_01x03_Pin; PinHeader_1x03_P2.54mm_Vertical
J2, J3: Conn_01x20_Pin; PinHeader_1x20_P2.54mm_Vertical
LOW_BATT1: SW_Push; SW_PUSH_6mm
LOW_OIL1: SW_Push; SW_PUSH_6mm
MCP2515_HEADER1: Conn_01x07_Socket; PinHeader_1x07_P2.54mm_Vertical
OIL_TEMP1: OIL_TEMP; Potentiometer_Alps_RK163_Single_Horizontal
R1: 249; R_1210_3225Metric_Pad1.30x2.65mm_HandSolder
R2: 120; R_1210_3225Metric_Pad1.30x2.65mm_HandSolder
RPM1: RPM; Potentiometer_Alps_RK163_Single_Horizontal
U1: SN65HVD230; SOIC-8_3.9x4.9mm_P1.27mm

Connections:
3V3: COOLANT_TEMP1.1, J2.5, OIL_TEMP1.1, RPM1.1, U1.3 (VCC)
5V: J2.1, MCP2515_HEADER1.7
ADC0: J2.10, RPM1.2
ADC1: J2.9, OIL_TEMP1.2
ADC2: COOLANT_TEMP1.2, J2.7
CAN_H: J1.1, R2.1, U1.7 (CANH)
CAN_L: J1.2, R2.2, U1.6 (CANL)
CAN_RX: J3.6, U1.4 (R)
CAN_STATUS: J3.4, R1.1
CAN_TX: J3.7, U1.1 (D)
GEAR_SHIFT: GEAR_SHIFT1.1, J2.12
GND: COOLANT_TEMP1.3, GEAR_SHIFT1.2, J1.3, J2.3, J2.13, LOW_BATT1.2, LOW_OIL1.2, MCP2515_HEADER1.6, OIL_TEMP1.3, RPM1.3, U1.2 (GND), U1.8 (Rs); also elsewhere on the board
LOW_12VBAT_VOLTAGE: J3.19, LOW_BATT1.1
LOW_OIL_PRESSURE: J3.20, LOW_OIL1.1
MCP2515_CS: J2.19, MCP2515_HEADER1.5
MCP2515_MISO: J2.20, MCP2515_HEADER1.4
MCP2515_MOSI: J2.16, MCP2515_HEADER1.3
MCP2515_SCK: J2.17, MCP2515_HEADER1.2
unnamed 18: R1.2; also elsewhere on the board

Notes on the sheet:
TERMINATOR (because it is at the edge of CAN BUS)
LED WILL BLINK IF CAN BUS IS ON
CAN_TRANSCIEVER
CONECTOR FOR CAN_H, CAN_L and remember GND also!
POTENTIOMETER: USER INPUT
RASPBERRY PI PICO
BUTTONS: USER INPUT

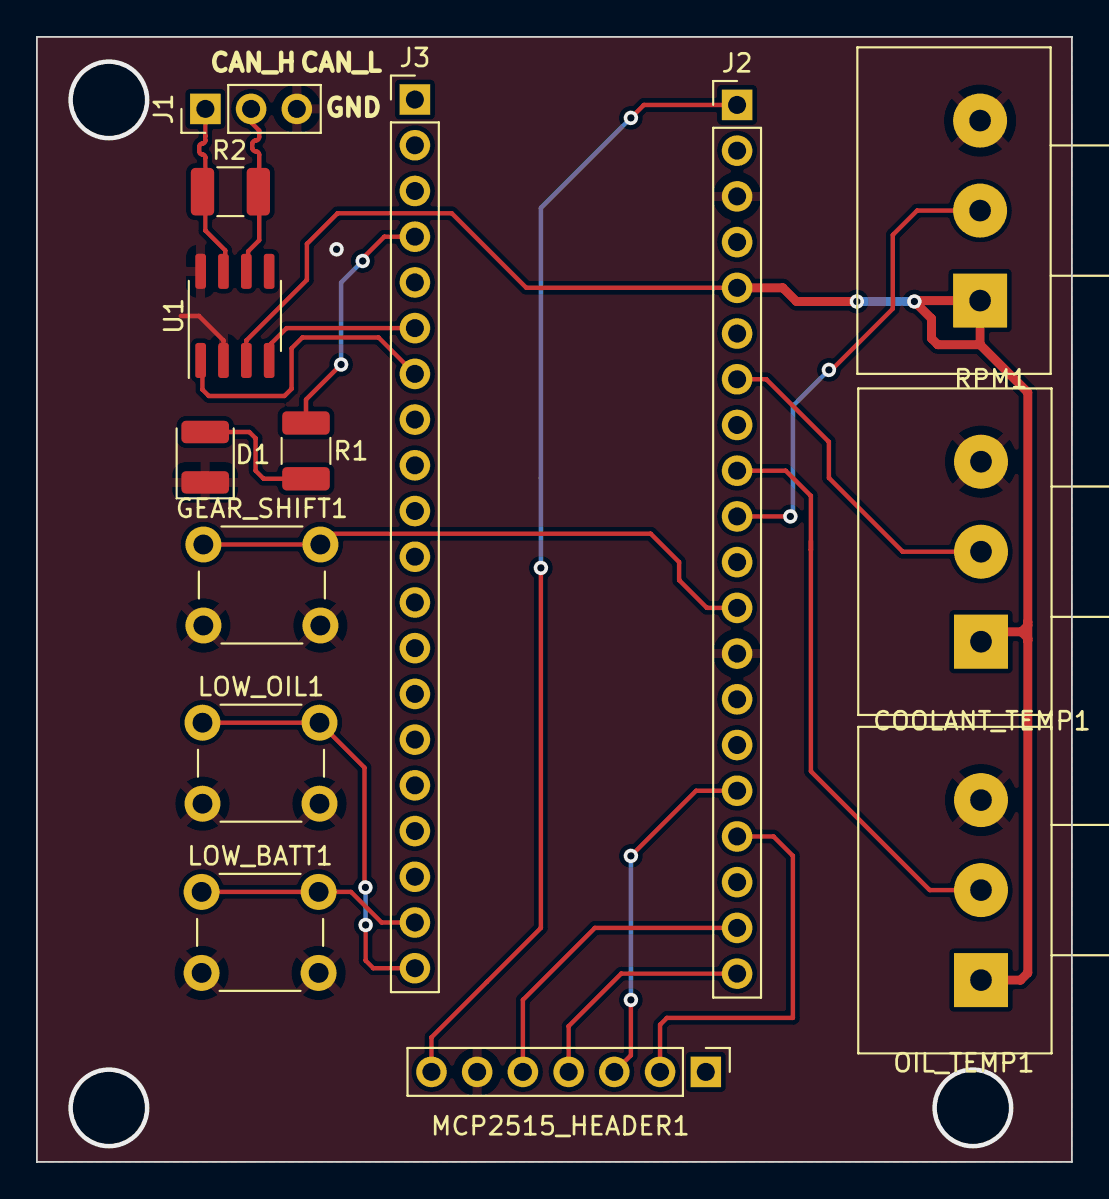
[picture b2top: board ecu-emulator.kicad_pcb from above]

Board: 2 copper layers, 57.5 x 62.5 mm, 14 parts (0 on the bottom side), 19 nets.

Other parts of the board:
D1: LED_GREEN; D_1210_3225Metric

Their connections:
GND: D1.1 (K); also elsewhere on the board
unnamed 18: D1.2 (A); also elsewhere on the board

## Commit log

2024-04-26 Initial commit
    Signed-off: tudor.marculescu@stud.etti.upb.ro
2024-06-29 feature: Add latest docs
